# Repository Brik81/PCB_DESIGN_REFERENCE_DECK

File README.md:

# PCB_DESIGN_REFERENCE_DECK

A collection of 15 credit-card-sized PCB reference cards for hardware engineers. They feature component
footprints, trace dimensions, PCB design rules, RF and antenna geometries, impedance calculations, electronic
formulas, package references and practical engineering tools. They are designed in KiCad for everyday use at the
electronics design bench.

Each card is a real, double-sided 2-layer board (85.60 × 53.98 × 1.0 mm, black mask, white silk, ENIG) with a
plated Ø4 mm ring hole, so all 15 stack on one ring. Land patterns are stock KiCad 10 library footprints, and
measurement features (rulers, track/space samples, drill gauge, annular rings, impedance coupons) are real
copper.

| # | card | # | card |
|---|---|---|---|
| 01 | PCB layout master | 09 | RF & antennas |
| 02 | SMD footprint master | 10 | Digital logic |
| 03 | QFP / BGA / fine pitch | 11 | Communication interfaces |
| 04 | Drill / via / mechanical | 12 | Component identification |
| 05 | Soldering & assembly | 13 | Test / debug |
| 06 | Analog design | 14 | PCB manufacturing & stack-up |
| 07 | Power & thermal | 15 | Formula master |
| 08 | Impedance / high speed | | |

Previews and per-card details: [documentation/BOARD_CATALOG.md](documentation/BOARD_CATALOG.md).

## Requirements

- KiCad 10 (`kicad-cli`). The default path is `C:\Program Files\KiCad\10.0\bin\kicad-cli.exe`; override it
  with the env `KICAD_CLI`. Footprints come from the KiCad library (override with `KICAD10_FOOTPRINT_DIR`).
- Python ≥ 3.11 (standard library only; `tomllib`).

Nothing calls an online service or an AI model at runtime.

## Usage

```
python tools/deck_manager.py build          # all cards: generate, fill zones, DRC, Gerbers, drills, previews, validate, docs
python tools/deck_manager.py build 9        # one card
python tools/deck_manager.py list           # DRC / validation status per card
python tools/deck_manager.py package        # output/packages/<card>.zip ready to upload to a fab
python tools/deck_manager.py test           # unit tests
```

The individual steps are `scripts/generate_boards.py`, `generate_manufacturing_files.py`,
`validate_boards.py` and `generate_documentation.py`.

## Layout

| path | content |
|---|---|
| `project/` | mechanical spec, design rules, fab constraints, graphic style, card list |
| `data/` | formula registry, package dimensions, engineering tables. Every entry has a source and a status |
| `scripts/deck/` | shared library: board writer, layout guard, graphics, engineering calculations; `cards/c01…c15` |
| `boards/<card>/` | generated KiCad project (`.kicad_pcb`, `.kicad_pro`, `board_meta.json`) |
| `output/` | Gerbers, drill files, DRC / validation reports, previews |
| `documentation/` | catalog, formulas, sources, validation report, manufacturing guide, mechanical design, unresolved decisions |
| `tests/` | `python -m unittest discover tests` |

## Data integrity

Values are not invented. Every printed table comes from `data/` with a cited source and a status (VERIFIED,
CROSS-CHECKED, SECONDARY, UNVERIFIED); see [SOURCES.md](documentation/SOURCES.md). Computed values (impedance,
IPC-2221 current, wavelengths, VSWR, via resistance) come from `scripts/deck/eng.py`, which is unit-tested.
Standards are cited, not reproduced. Impedance and RF numbers are closed-form estimates for an **assumed**
εr = 4.5. Read [UNRESOLVED_DECISIONS.md](documentation/UNRESOLVED_DECISIONS.md) before relying on them or
ordering.

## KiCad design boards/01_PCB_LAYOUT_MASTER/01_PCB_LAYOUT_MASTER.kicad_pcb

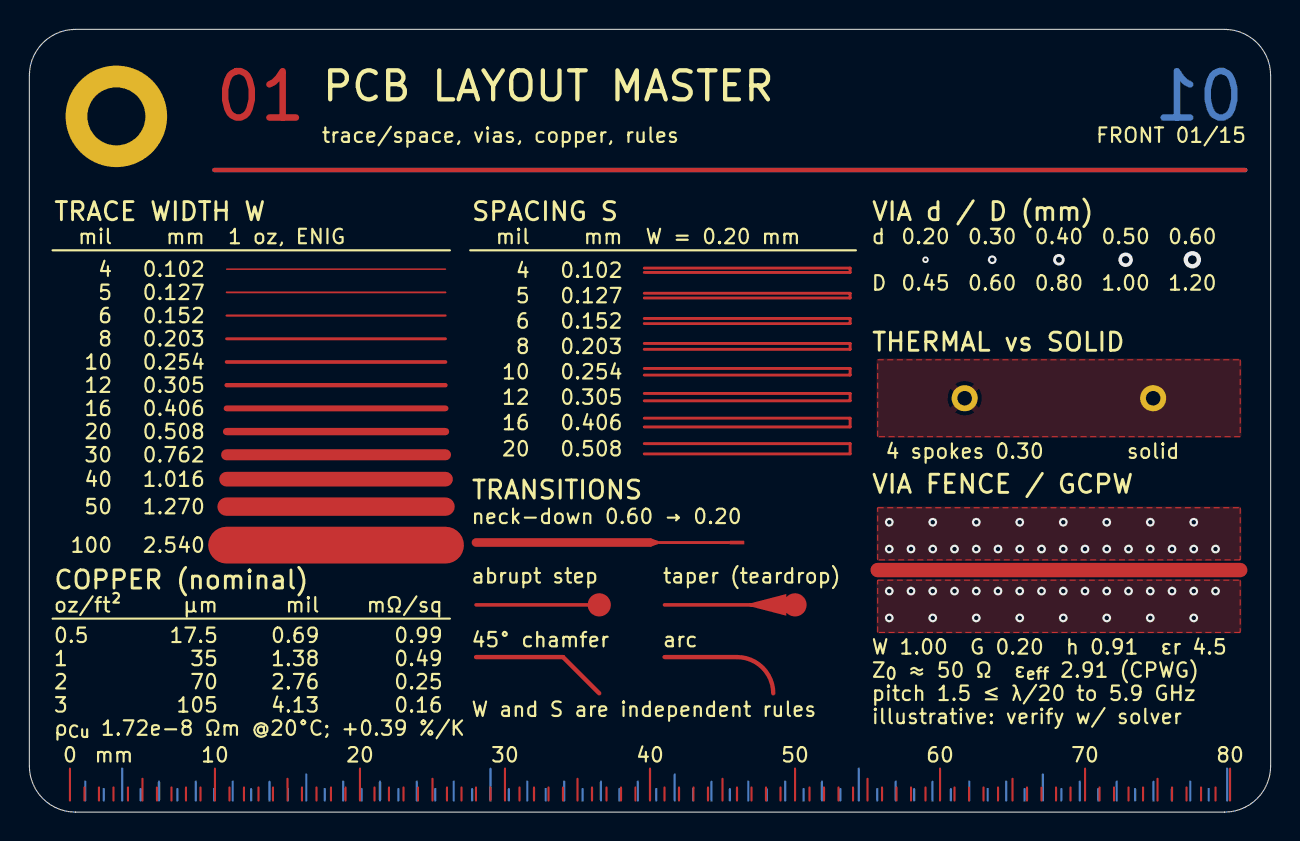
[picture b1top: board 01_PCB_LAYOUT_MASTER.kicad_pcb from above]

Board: 2 copper layers, 85.6 x 54.0 mm, 8 parts (0 on the bottom side), 3 nets.

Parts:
H1: RING_HOLE
P2, P3, P4, P5, P6, P7, P8: PAD

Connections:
PLANE_A: P7.1, P8.1
REF21: P2.1, P3.1
REF23: P5.1, P6.1

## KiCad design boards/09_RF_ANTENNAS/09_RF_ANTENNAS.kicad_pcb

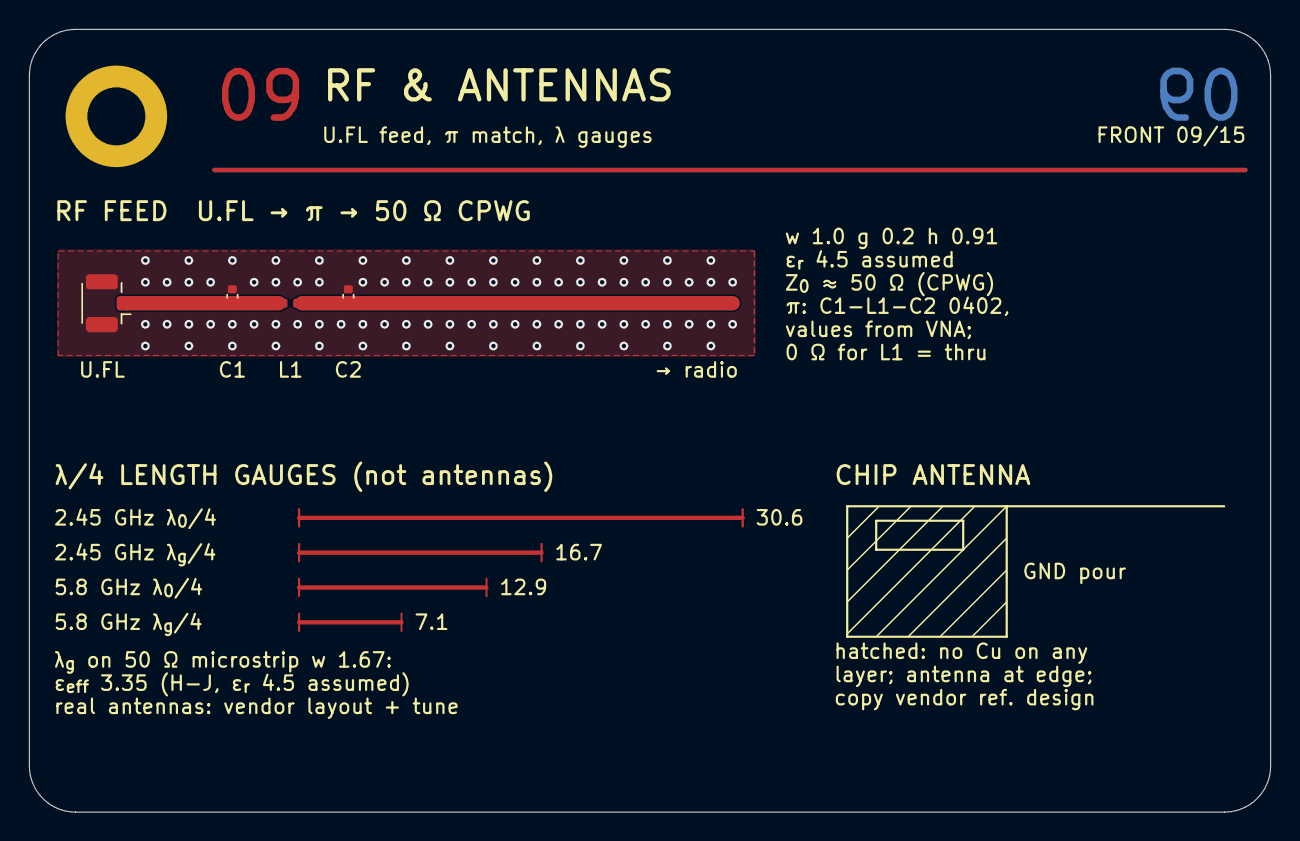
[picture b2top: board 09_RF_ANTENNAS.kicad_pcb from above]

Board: 2 copper layers, 85.6 x 54.0 mm, 5 parts (0 on the bottom side), 3 nets.

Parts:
H1: RING_HOLE
U2: U.FL_Hirose_U.FL-R-SMT-1_Vertical
U3: L_0402_1005Metric
U4, U5: C_0402_1005Metric

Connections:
GND_RF: U2.2, U4.2, U5.2
RF_A: U2.1, U3.1, U4.1
RF_B: U3.2, U5.1

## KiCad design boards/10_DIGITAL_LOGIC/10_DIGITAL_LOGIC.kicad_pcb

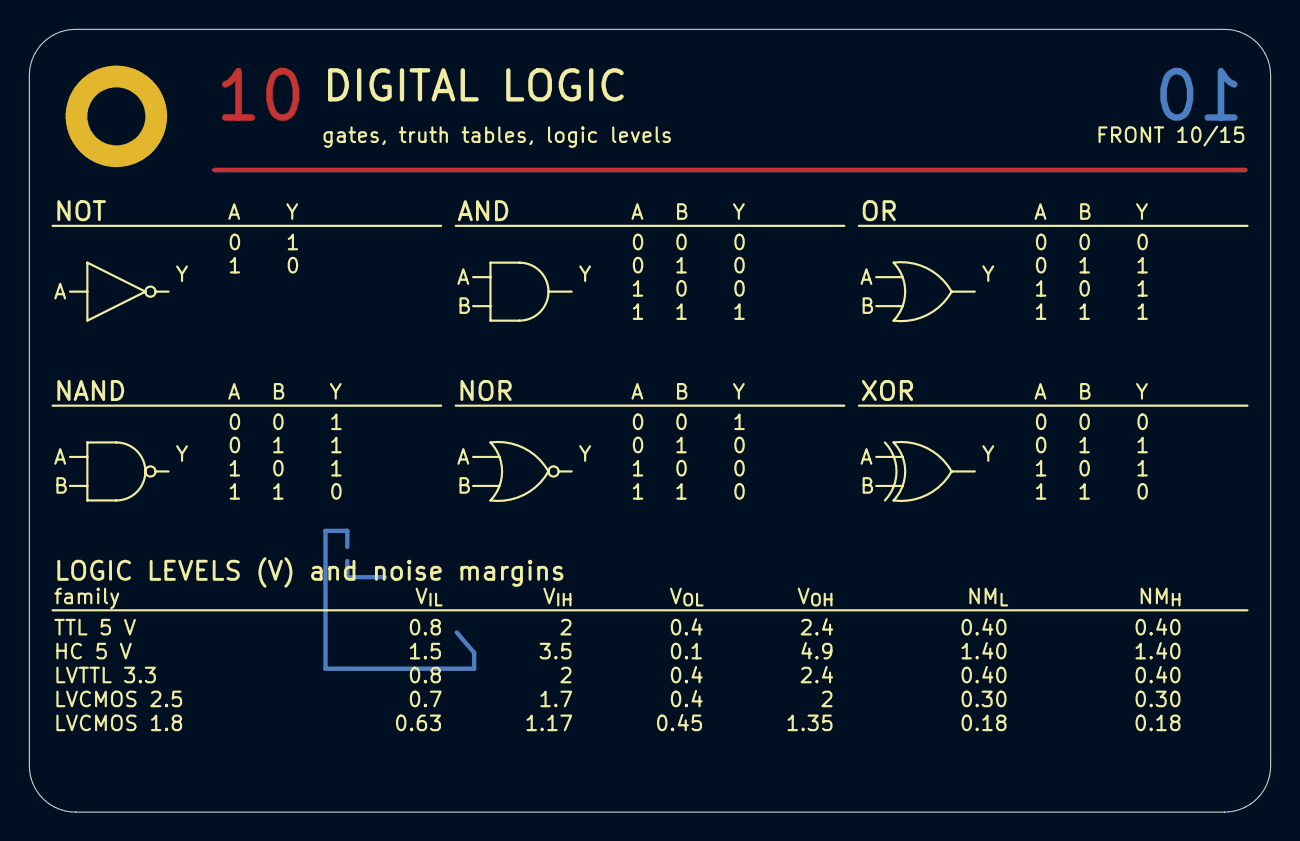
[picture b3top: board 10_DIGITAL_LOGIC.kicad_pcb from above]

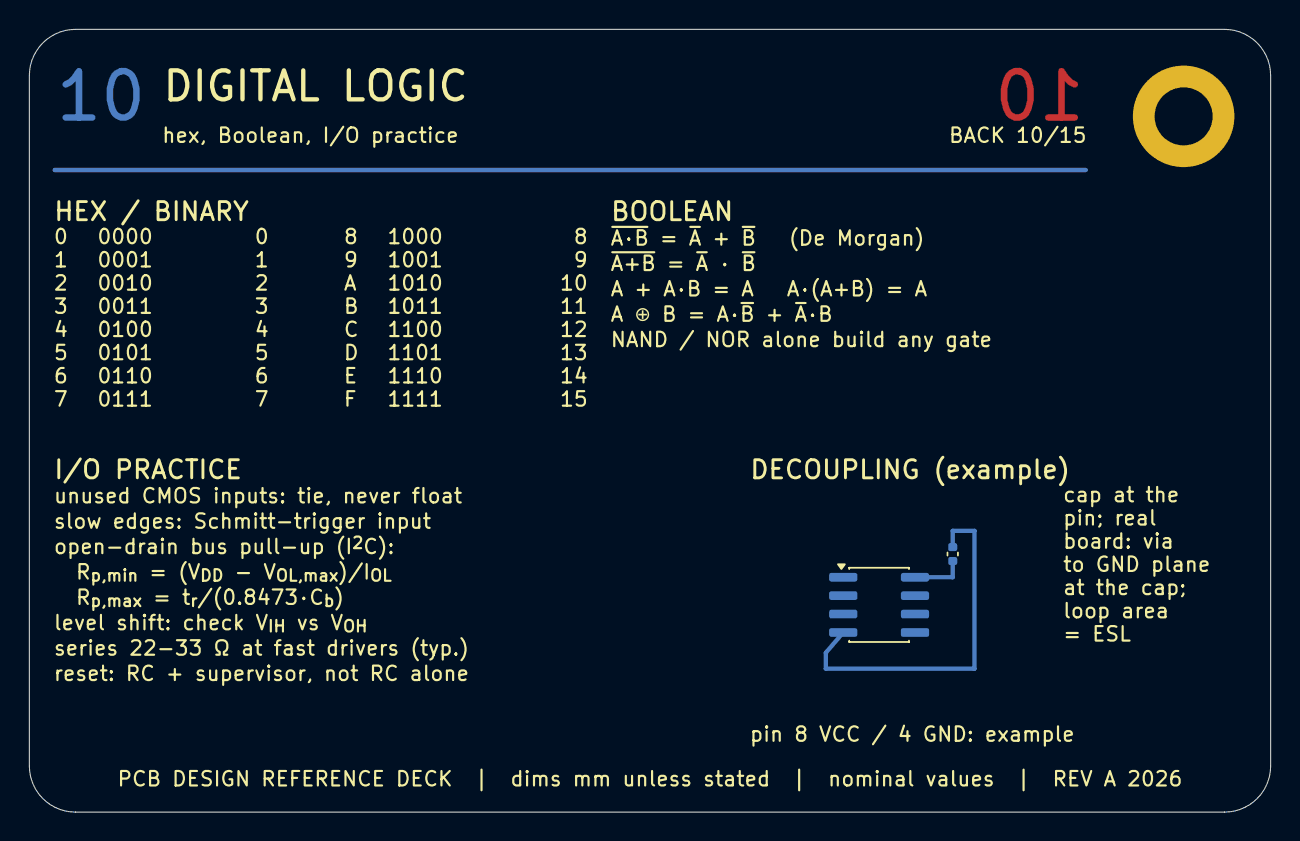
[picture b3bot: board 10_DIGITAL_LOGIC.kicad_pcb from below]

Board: 2 copper layers, 85.6 x 54.0 mm, 3 parts (2 on the bottom side), 2 nets.

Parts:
H1: RING_HOLE
U2: SOIC-8_3.9x4.9mm_P1.27mm
U3: C_0402_1005Metric

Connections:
GND_DEMO: U2.4, U3.2
VCC_DEMO: U2.8, U3.1
